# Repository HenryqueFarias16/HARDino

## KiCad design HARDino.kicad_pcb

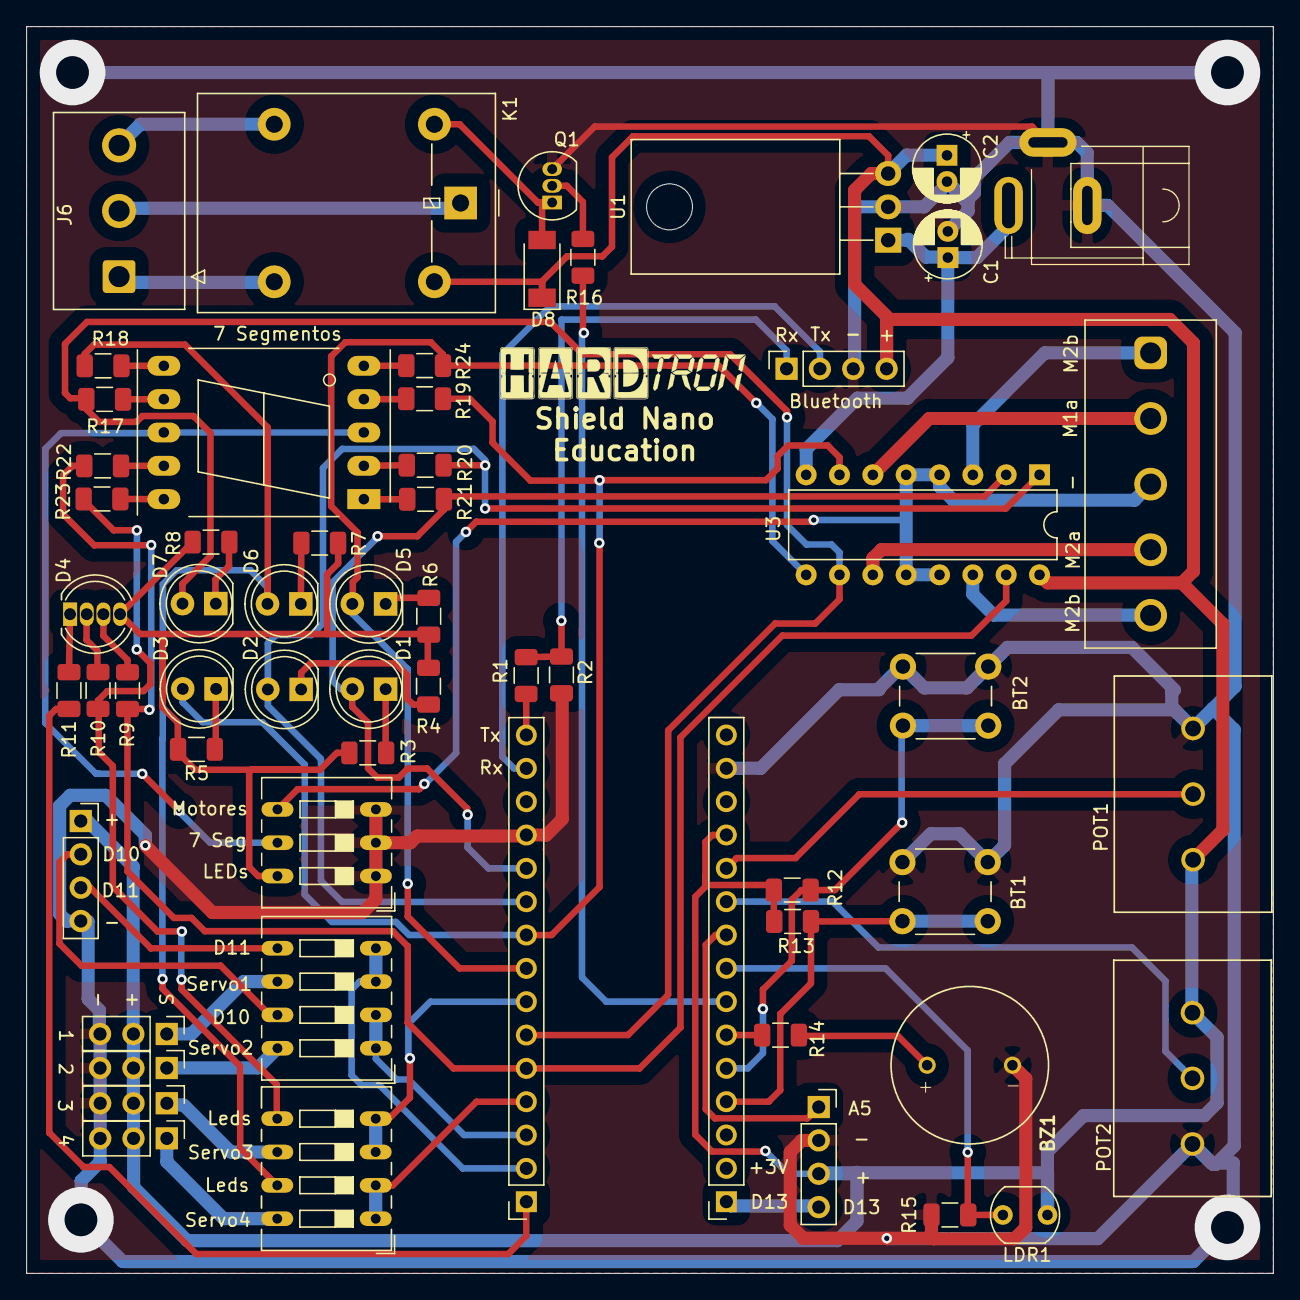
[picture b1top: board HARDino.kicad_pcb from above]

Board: 2 copper layers, 95.0 x 95.0 mm, 60 parts (0 on the bottom side), 64 nets.

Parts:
BT1, BT2: SW_Push; SW_PUSH_6mm_H5mm
BZ1: Buzzer
C1, C2: 100uF; CP_Radial_D5.0mm_P2.00mm
D1, D2, D3, D5, D6, D7: LED; LED_D5.0mm
D4: LED_RGBC; LED_D5.0mm-4_RGB
D8: 1N4007; D_SOD-128
J1: RAPC712; SPC4078
J2, J5, J10: Conn_01x04; PinSocket_1x04_P2.54mm_Vertical
J3, J4, J11, J12: Conn_01x03; PinHeader_1x03_P2.54mm_Vertical
J6: Conn_01x03; Borne_1x3_10x15mm
J7, J8: Conn_01x15; PinSocket_1x15_P2.54mm_Vertical
J9: Conn_01x05; Borne_1x5_10x25mm
K1: G5LE-1; Relay_5v-250V.10A
LDR1: LDR07; R_LDR_5.1x4.3mm_P3.4mm_Vertical
POT1, POT2: 10k; Potenciometro
Q1: BC547; TO-92_Inline
R1, R16: 1k; R_1206_3216Metric
R2: 2k; R_1206_3216Metric
R3, R4, R5, R6, R7, R8, R9, R10, R11, R17, R18, R19, R20, R21, R22, R23, R24: 330; R_1206_3216Metric
R12, R13, R15: 10k; R_1206_3216Metric
R14: 100; R_1206_3216Metric
SW1, SW6: SW_DIP_x04; SW_DIP_SPSTx04_Slide_9.78x12.34mm_W8.61mm_P2.54mm
SW4: SW_DIP_x03; SW_DIP_SPSTx03_Slide_9.78x9.8mm_W8.61mm_P2.54mm
U1: uA7805; TO-220-3_Horizontal_TabDown
U2: SM420561N; 7SegmentLED_LTS6760_LTS6780
U3: L293D; DIP-16_W7.62mm

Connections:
7seg: SW4.5, U2.3, U2.8
+5V: C2.1, D8.1, J2.1, J3.2, J4.2, J5.3, J7.12, J10.4, J11.2, J12.2, K1.5, LDR1.2, POT1.3, POT2.3, R12.1, R13.1, U1.3, U3.16
A0: BT1.2, J7.4, R12.2
A1: BT2.2, J7.5, R13.2
A2: J7.6, R14.1
A3: J7.7, R16.2
A4: J7.8, LDR1.1, R15.2
A5: J5.1, J7.9
A6: J7.10, POT2.2
A7: J7.11, POT1.2
D2: D1.2, J8.11, R21.2, U3.2
D3: D2.2, J8.10, R20.2, U3.1
D4: D3.2, J8.9, R19.2, U3.7
D5: D5.2, J8.8, R24.2, U3.9
D6: J8.7, SW1.3, SW1.4
D7: D7.2, J8.6, R17.2, U3.10
D8: J8.5, R9.2, R22.2, U3.15
D9: J8.4, SW1.1, SW1.2
D10: J8.3, SW6.1, SW6.2
D11: J8.2, SW6.3, SW6.4
D12: J8.1, R11.2
D13: J5.4, J7.1
GND: BT1.1, BT2.1, BZ1.2, C1.2, C2.2, J1.1, J1.2, J2.4, J3.3, J4.3, J5.2, J7.14, J8.12, J10.3, J11.3, J12.3, POT1.1, POT2.1, Q1.3, R2.1, R15.1, SW4.1, SW4.2, SW4.3, U1.2
I.O1: J2.2, SW6.7
I.O2: J2.3, SW6.5
unnamed: BZ1.1, R14.2
unnamed: D1.1, R3.1
unnamed: D2.1, R4.1
unnamed: D3.1, R5.1
unnamed: D4.1, R11.1
unnamed: D4.2, R10.1
unnamed: D4.3, R9.1
unnamed: D5.1, R6.1
unnamed: D6.1, R7.1
unnamed: D7.1, R8.1
unnamed: D8.2, K1.2, Q1.1
unnamed: J6.1, K1.4
unnamed: J6.2, K1.1
unnamed: J6.3, K1.3
unnamed: J9.1, U3.3
unnamed: J9.2, U3.6
unnamed: J9.4, U3.11
unnamed: J9.5, U3.14
unnamed: Q1.2, R16.1
unnamed: R17.1, U2.7
unnamed: R18.1, U2.6
unnamed: R19.1, U2.4
unnamed: R20.1, U2.2
unnamed: R21.1, U2.1
unnamed: R22.1, U2.9
unnamed: R23.1, U2.10
unnamed: R24.1, U2.5
P1: D4.4, R3.2, R4.2, R5.2, R6.2, R7.2, R8.2, SW4.6
PonteH: J9.3, SW4.4, U3.4, U3.5, U3.12, U3.13
RX: J8.14, J10.2
RX-HC06: J10.1, R1.1, R2.2
TX: J8.15, R1.2
Vin: C1.1, J1.3, U1.1, U3.8
p4: D6.2, R18.2, SW1.7
p5: R10.2, R23.2, SW1.5
servo1: J3.1, SW6.8
servo2: J4.1, SW6.6
servo3: J11.1, SW1.6
servo4: J12.1, SW1.8
